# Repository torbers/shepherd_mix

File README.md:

# shepherd_mix
modular music hardware system for everyone

---

License:

<a href="https://github.com/torbers/shepherd_mix">Shepherd Mix design specifications</a> © 2025 by <a href="http://sambkothe.com">Sam Kothe (torbers)</a> are licensed under <a href="https://creativecommons.org/licenses/by-sa/4.0/">CC BY-SA 4.0</a>

<a href="https://github.com/torbers/shepherd_mix">Shepherd Mix code</a> © 2025 by <a href="http://sambkothe.com">Sam Kothe (torbers)</a> is licensed under <a href="https://creativecommons.org/licenses/by-sa/4.0/">CC BY-SA 4.0</a>

<a href="https://github.com/torbers/shepherd_mix">Shepherd Mix PCB designs</a> © 2025 by <a href="http://sambkothe.com">Sam Kothe (torbers)</a> are licensed under <a href="https://creativecommons.org/licenses/by-nc-sa/4.0/">CC BY-NC-SA 4.0</a>

<a href="https://github.com/torbers/shepherd_mix">Shepherd Mix art</a> © 2025 by <a href="http://sambkothe.com">Sam Kothe (torbers)</a> is licensed under <a href="https://creativecommons.org/licenses/by-nc-sa/4.0/">CC BY-NC-SA 4.0</a>

This means that you may design, manufacture, and sell products compatible with Shepherd Mix or using its code in accordance with [open source standards](https://opensource.org/osd), but you may not sell my PCB source files, artistic designs, or products made with them. In any case, you must give [appropriate credit](https://creativecommons.org/licenses/by-sa/4.0/#ref-appropriate-credit).

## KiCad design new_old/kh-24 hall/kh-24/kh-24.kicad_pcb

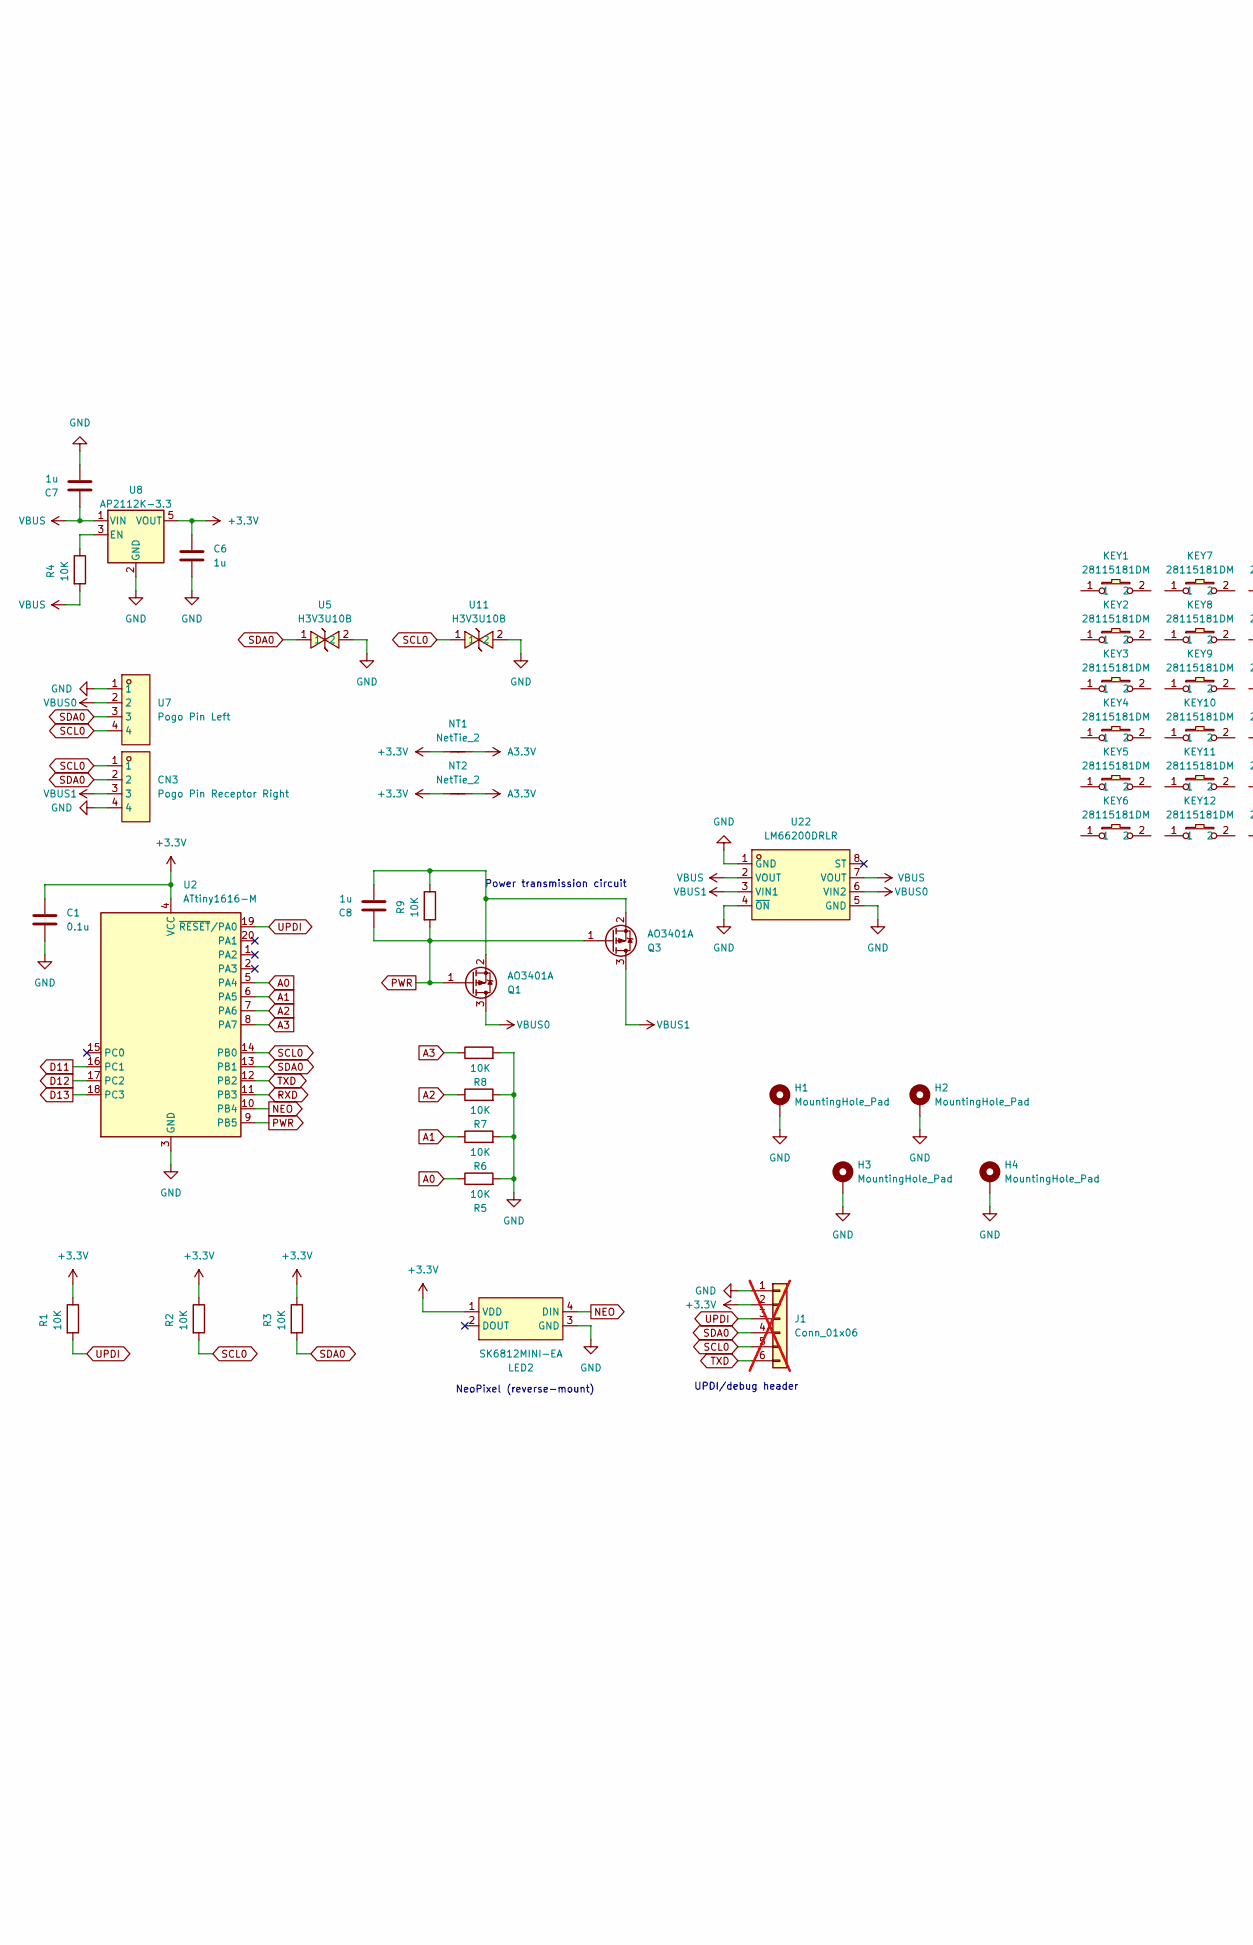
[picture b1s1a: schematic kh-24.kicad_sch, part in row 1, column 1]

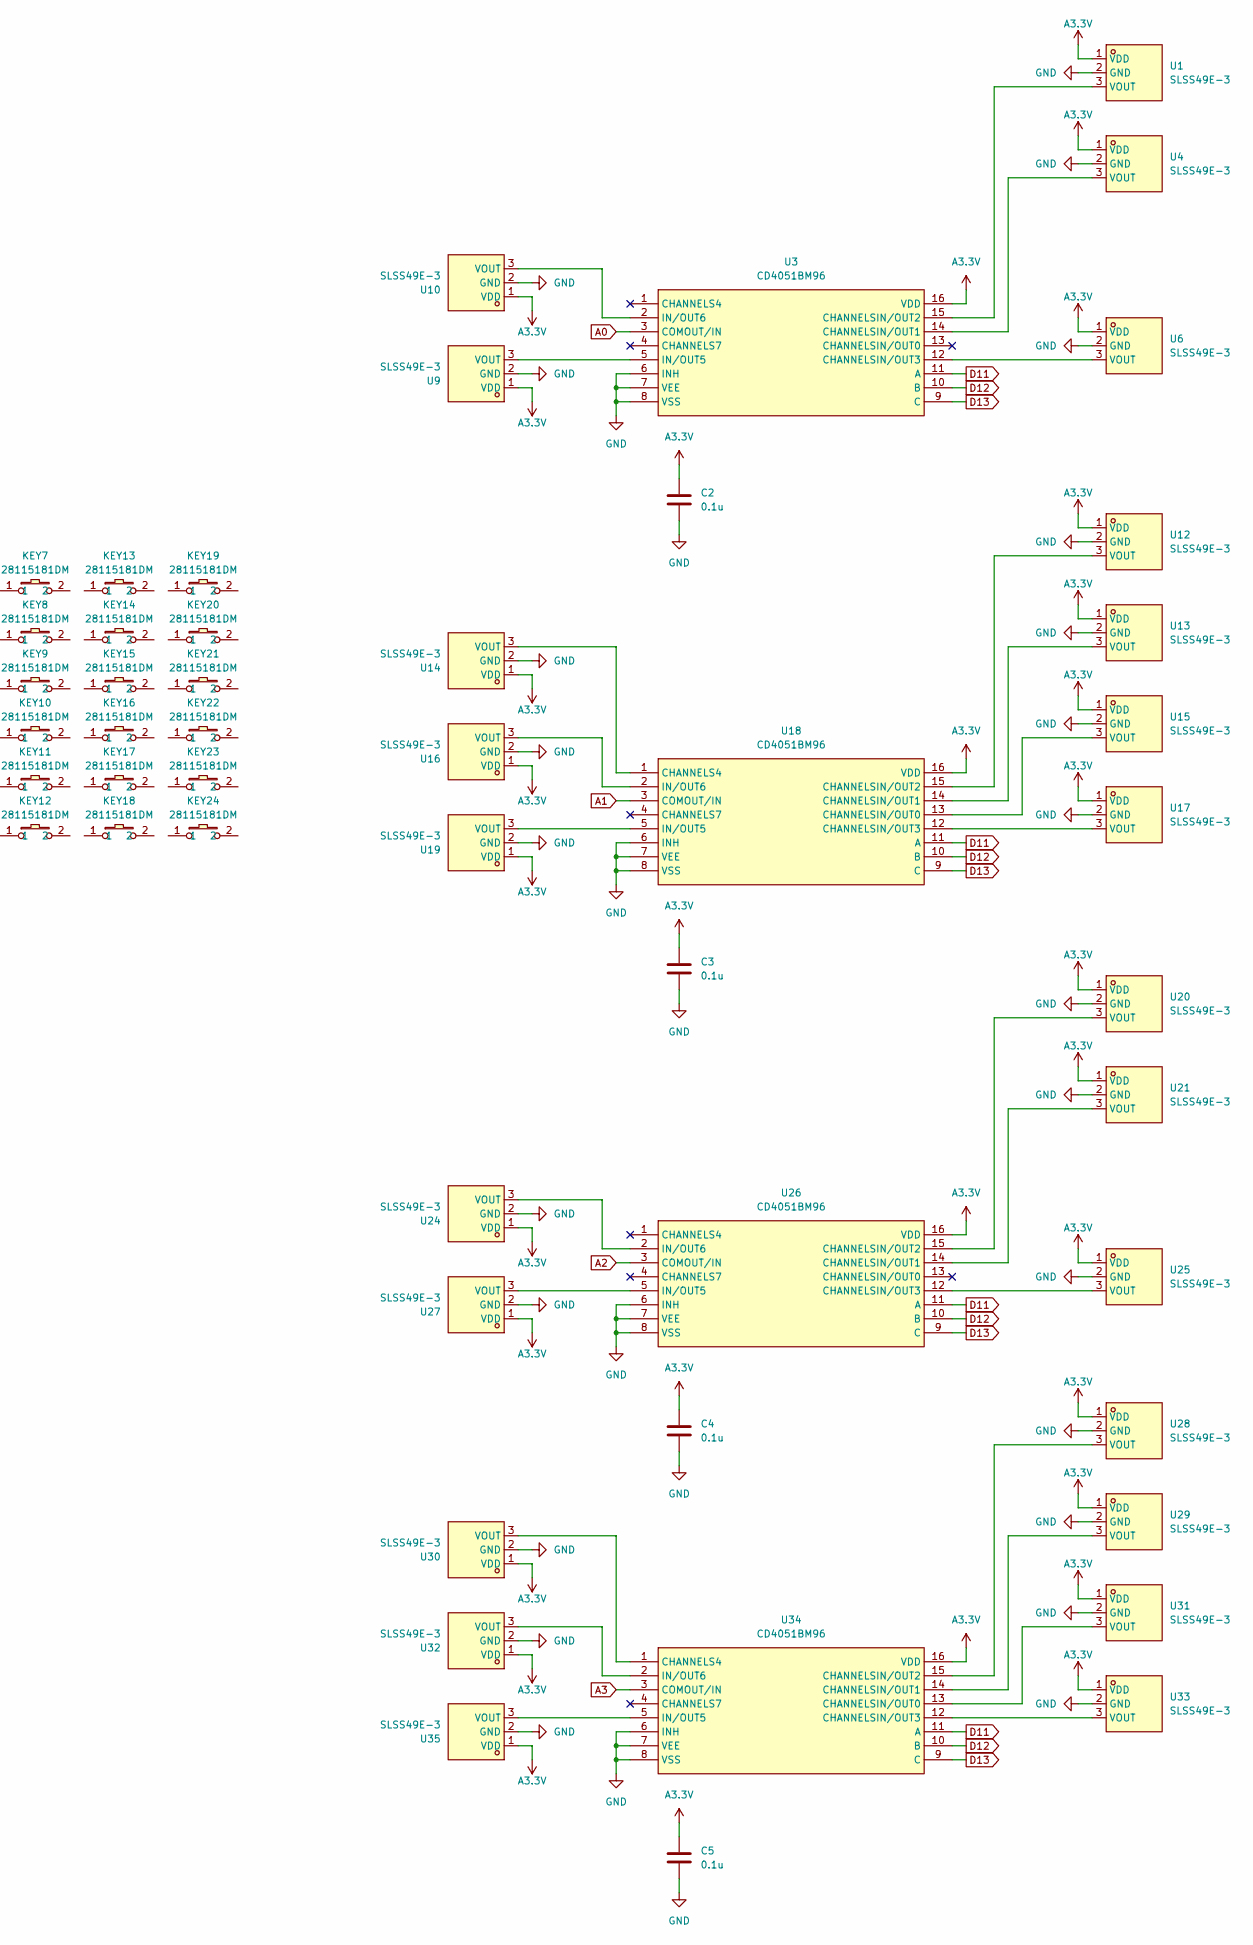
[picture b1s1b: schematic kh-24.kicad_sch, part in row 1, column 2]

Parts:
C1, C2, C3, C4, C5: 0.1u; C_0402_1005Metric
C6, C7, C8: 1u; C_0402_1005Metric
CN3: Pogo Pin Receptor Right; CONN-SMD_YZ199315035T-04025-01; LCSC Part C5296825
H1, H2, H3, H4: MountingHole_Pad; MountingHole_2.7mm_M2.5_DIN965_Pad_TopBottom
J1: Conn_01x06; PinHeader_1x06_P2.54mm_Vertical; not fitted
KEY1, KEY2, KEY3, KEY4, KEY5, KEY6, KEY7, KEY8, KEY9, KEY10, KEY11, KEY12, KEY13, KEY14, KEY15, KEY16, KEY17, KEY18, KEY19, KEY20, KEY21, KEY22, KEY23, KEY24: 28115181DM; hall_key_footprint; LCSC Part C47121944
LED2: SK6812MINI-EA; LED-SMD_4P-L3.2-W2.8_SK6812MINI-EA; LCSC Part C5378731
NT1, NT2: NetTie_2; NetTie-2_SMD_Pad0.5mm
Q1, Q3: AO3401A; SOT-23
R1, R2, R3, R4, R9: 10K; R_0402_1005Metric
R5, R6, R7, R8: 10K; R_0402_1005Metric_Pad0.72x0.64mm_HandSolder
U1, U4, U6, U9, U10, U12, U13, U14, U15, U16, U17, U19, U20, U21, U24, U25, U27, U28, U29, U30, U31, U32, U33, U35: SLSS49E-3; SLSS49E_Hall_Switch_MX; LCSC Part C2904393
U2: ATtiny1616-M; VQFN-20-1EP_3x3mm_P0.4mm_EP1.7x1.7mm
U3, U18, U26, U34: CD4051BM96; SOIC-16_L9.9-W3.9-P1.27-LS6.0-BL; LCSC Part C21379
U5, U11: H3V3U10B; DFN1006-2L-BI; LCSC Part C20615782
U7: Pogo Pin Left; CONN-SMD_4P-L11.0-W5.5-P2.50_YZ165615055F-04025-01; LCSC Part C5296819
U8: AP2112K-3.3; SOT-23-5
U22: LM66200DRLR; SOT-583-8_L2.1-W1.2-P0.50-LS1.6-BL; LCSC Part C3235556

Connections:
+3.3V: C1.1, C6.1, J1.2, LED2.1 (VDD), NT1.1, NT2.1, R1.1, R2.1, R3.1, U2.4 (VCC), U8.5 (VOUT)
A0: R5.1, U2.5 (PA4), U3.3 (COMOUT/IN)
A1: R6.1, U2.6 (PA5), U18.3 (COMOUT/IN)
A2: R7.1, U2.7 (PA6), U26.3 (COMOUT/IN)
A3: R8.1, U2.8 (PA7), U34.3 (COMOUT/IN)
A3.3V: C2.1, C3.1, C4.1, C5.1, NT1.2, NT2.2, U1.1 (VDD), U3.16 (VDD), U4.1 (VDD), U6.1 (VDD), U9.1 (VDD), U10.1 (VDD), U12.1 (VDD), U13.1 (VDD), U14.1 (VDD), U15.1 (VDD), U16.1 (VDD), U17.1 (VDD), U18.16 (VDD), U19.1 (VDD), U20.1 (VDD), U21.1 (VDD), U24.1 (VDD), U25.1 (VDD), U26.16 (VDD), U27.1 (VDD), U28.1 (VDD), U29.1 (VDD), U30.1 (VDD), U31.1 (VDD), U32.1 (VDD), U33.1 (VDD), U34.16 (VDD), U35.1 (VDD)
D11: U2.16 (PC1), U3.11 (A), U18.11 (A), U26.11 (A), U34.11 (A)
D12: U2.17 (PC2), U3.10 (B), U18.10 (B), U26.10 (B), U34.10 (B)
D13: U2.18 (PC3), U3.9 (C), U18.9 (C), U26.9 (C), U34.9 (C)
GND: C1.2, C2.2, C3.2, C4.2, C5.2, C6.2, C7.2, CN3.4, H1.1, H2.1, H3.1, H4.1, J1.1, LED2.3 (GND), R5.2, R6.2, R7.2, R8.2, U1.2 (GND), U2.3 (GND), U2.21 (GND), U3.6 (INH), U3.7 (VEE), U3.8 (VSS), U4.2 (GND), U5.2, U6.2 (GND), U7.1, U8.2 (GND), U9.2 (GND), U10.2 (GND), U11.2, U12.2 (GND), U13.2 (GND), U14.2 (GND), U15.2 (GND), U16.2 (GND), U17.2 (GND), U18.6 (INH), U18.7 (VEE), U18.8 (VSS), U19.2 (GND), U20.2 (GND), U21.2 (GND), U22.1 (GND), U22.4 (~ON), U22.5 (GND), U24.2 (GND), U25.2 (GND), U26.6 (INH), U26.7 (VEE), U26.8 (VSS), U27.2 (GND), U28.2 (GND), U29.2 (GND), U30.2 (GND), U31.2 (GND), U32.2 (GND), U33.2 (GND), U34.6 (INH), U34.7 (VEE), U34.8 (VSS), U35.2 (GND)
NEO: LED2.4 (DIN), U2.10 (PB4)
unnamed: C8.2, Q1.2 (S), Q3.2 (S), R9.1
unnamed: U1.3 (VOUT), U3.15 (CHANNELSIN/OUT2)
unnamed: U3.14 (CHANNELSIN/OUT1), U4.3 (VOUT)
unnamed: U3.12 (CHANNELSIN/OUT3), U6.3 (VOUT)
unnamed: U3.5 (IN/OUT5), U9.3 (VOUT)
unnamed: R4.1, U8.3 (EN)
unnamed: U3.2 (IN/OUT6), U10.3 (VOUT)
unnamed: U12.3 (VOUT), U18.15 (CHANNELSIN/OUT2)
unnamed: U13.3 (VOUT), U18.14 (CHANNELSIN/OUT1)
unnamed: U14.3 (VOUT), U18.1 (CHANNELS4)
unnamed: U15.3 (VOUT), U18.13 (CHANNELSIN/OUT0)
unnamed: U16.3 (VOUT), U18.2 (IN/OUT6)
unnamed: U17.3 (VOUT), U18.12 (CHANNELSIN/OUT3)
unnamed: U18.5 (IN/OUT5), U19.3 (VOUT)
unnamed: U20.3 (VOUT), U26.15 (CHANNELSIN/OUT2)
unnamed: U21.3 (VOUT), U26.14 (CHANNELSIN/OUT1)
unnamed: U24.3 (VOUT), U26.2 (IN/OUT6)
unnamed: U25.3 (VOUT), U26.12 (CHANNELSIN/OUT3)
unnamed: U26.5 (IN/OUT5), U27.3 (VOUT)
unnamed: U28.3 (VOUT), U34.15 (CHANNELSIN/OUT2)
unnamed: U29.3 (VOUT), U34.14 (CHANNELSIN/OUT1)
unnamed: U30.3 (VOUT), U34.1 (CHANNELS4)
unnamed: U31.3 (VOUT), U34.13 (CHANNELSIN/OUT0)
unnamed: U32.3 (VOUT), U34.2 (IN/OUT6)
unnamed: U33.3 (VOUT), U34.12 (CHANNELSIN/OUT3)
unnamed: U34.5 (IN/OUT5), U35.3 (VOUT)
PWR: C8.1, Q1.1 (G), Q3.1 (G), R9.2, U2.9 (PB5)
RXD: U2.11 (PB3)
SCL0: CN3.1, J1.5, R2.2, U2.14 (PB0), U7.4, U11.1
SDA0: CN3.2, J1.4, R3.2, U2.13 (PB1), U5.1, U7.3
TXD: J1.6, U2.12 (PB2)
UPDI: J1.3, R1.2, U2.19 (~RESET/PA0)
VBUS: C7.1, R4.2, U8.1 (VIN), U22.2 (VOUT), U22.7 (VOUT)
VBUS0: Q1.3 (D), U7.2, U22.6 (VIN2)
VBUS1: CN3.3, Q3.3 (D), U22.3 (VIN1)

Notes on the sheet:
Power transmission circuit
NeoPixel (reverse-mount)
UPDI/debug header

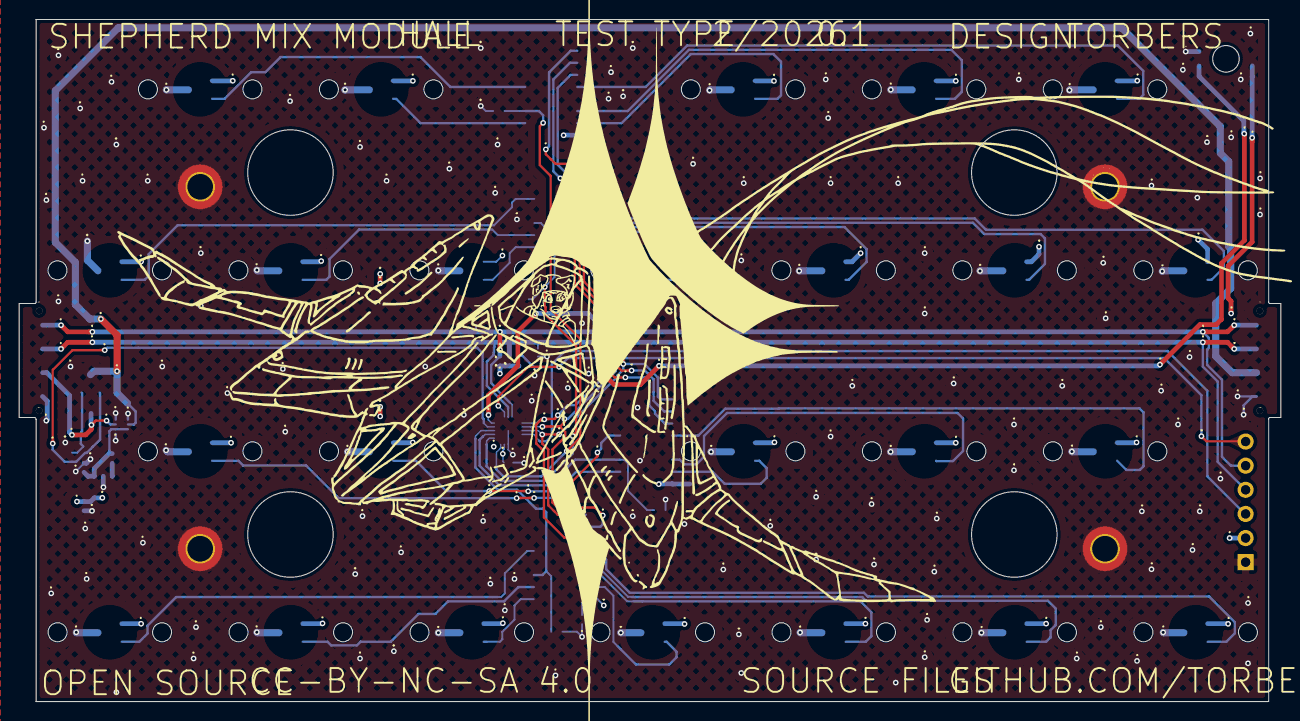
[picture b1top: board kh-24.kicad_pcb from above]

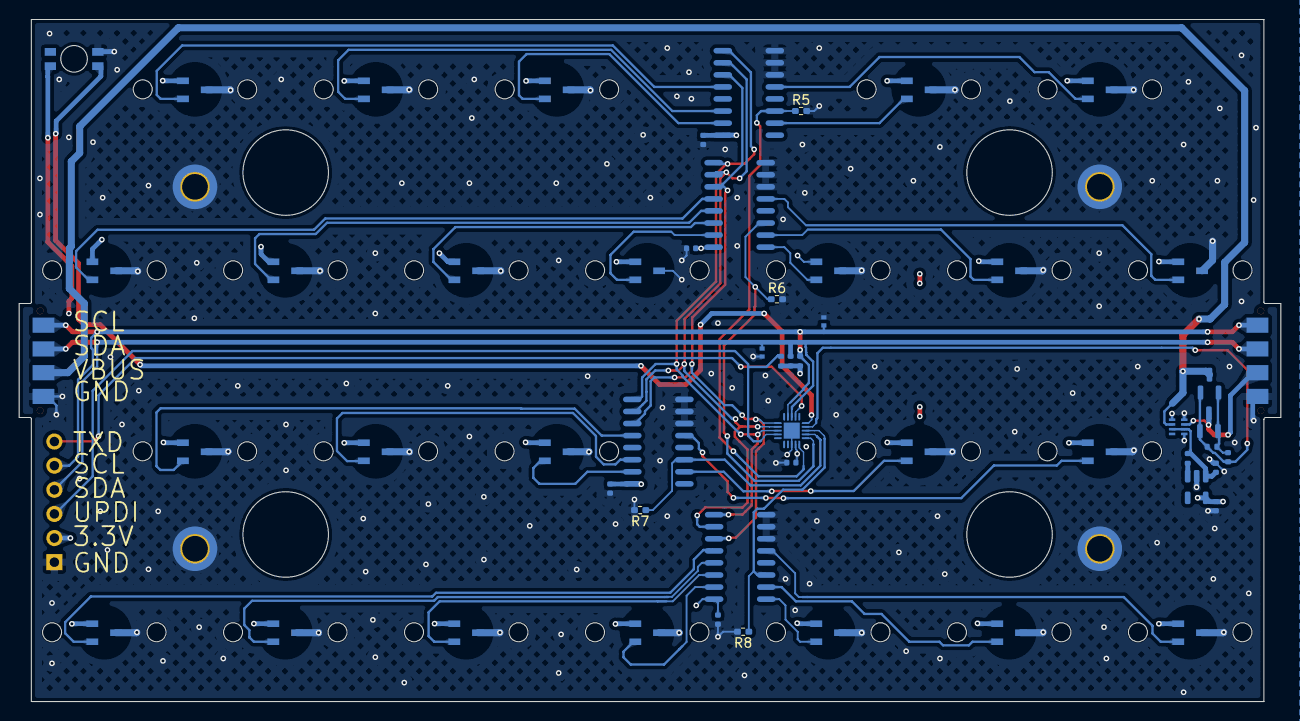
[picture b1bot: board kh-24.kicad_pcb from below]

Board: 4 copper layers, 132.8 x 71.8 mm, 86 parts (60 on the bottom side), 45 nets.

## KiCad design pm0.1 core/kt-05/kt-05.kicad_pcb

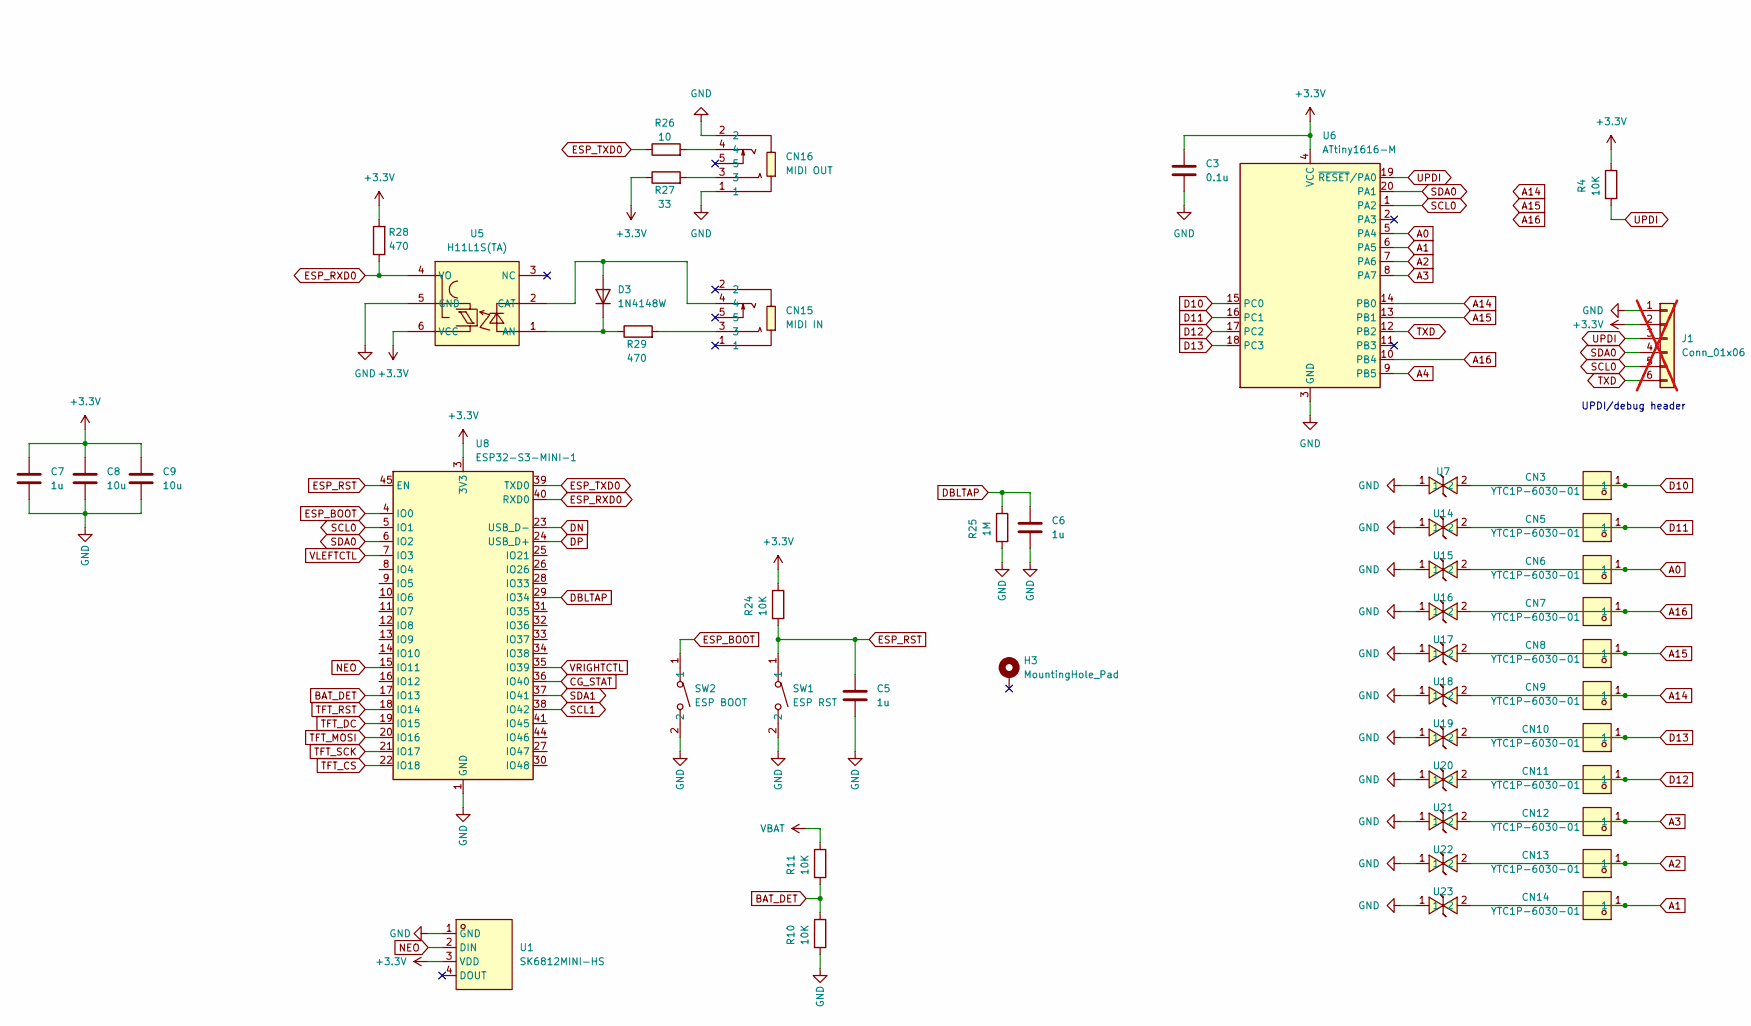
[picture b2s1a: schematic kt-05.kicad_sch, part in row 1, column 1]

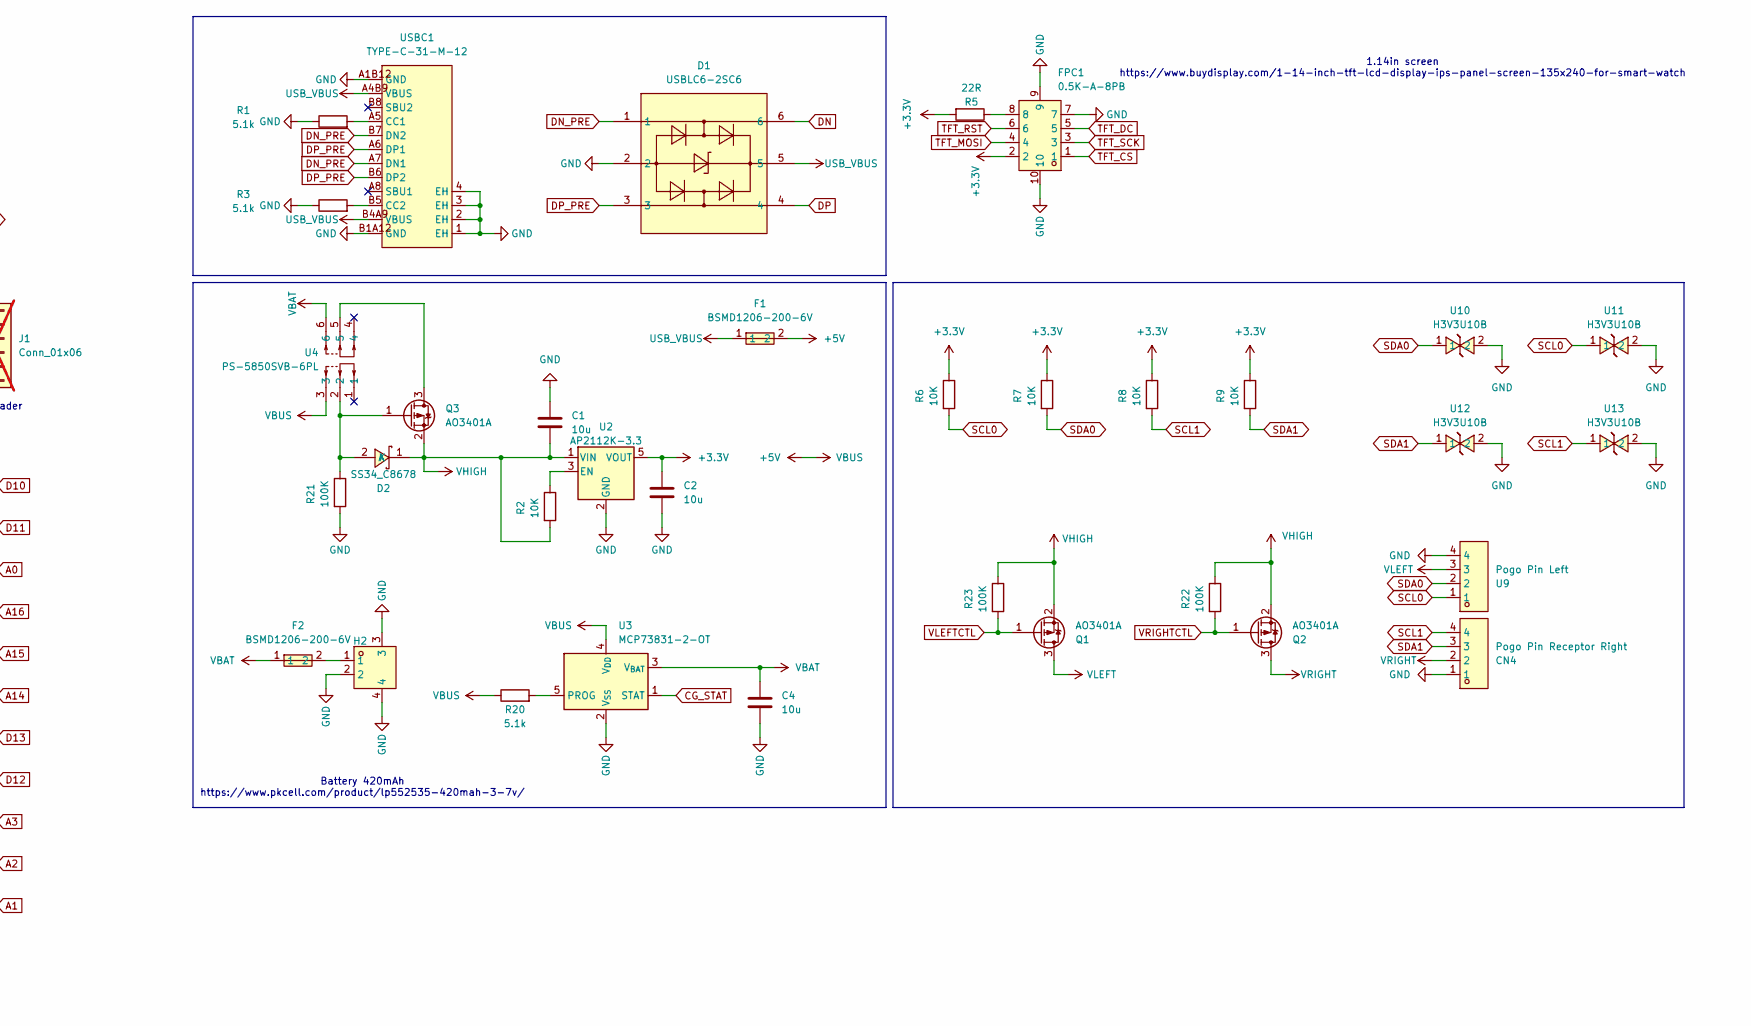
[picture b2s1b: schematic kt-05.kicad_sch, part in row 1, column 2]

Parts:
C1, C2, C4, C8, C9: 10u; C_0402_1005Metric
C3: 0.1u; C_0402_1005Metric
C5, C6, C7: 1u; C_0402_1005Metric
CN3, CN5, CN6, CN7, CN8, CN9, CN10, CN11, CN12, CN13, CN14: YTC1P-6030-01; SMD-1_BD2.0-H10.0; LCSC Part C5221285
CN4: Pogo Pin Receptor Right; CONN-SMD_YZ199315035T-04025-01; LCSC Part C5296825
CN15: MIDI IN; AUDIO-SMD_PJ-327A5JJ; LCSC Part C668605
CN16: MIDI OUT; AUDIO-SMD_PJ-327A5JJ; LCSC Part C668605
D1: USBLC6-2SC6; SOT-23-6_L2.9-W1.6-P0.95-LS2.8-BL; LCSC Part C7519
D2: SS34_C8678; SMA_L4.3-W2.6-LS5.2-RD; LCSC Part C8678
D3: 1N4148W; D_SOD-123
F1, F2: BSMD1206-200-6V; F1206; LCSC Part C883134
FPC1: 0.5K-A-8PB; FPC-SMD_8P-P0.50_HDGC_0.5K-A-8PB; LCSC Part C2914134
H2: WAFER-PH2.0-2PWB; CONN-SMD_2P-P2.00_XUNPU_WAFER-PH2.0-2PWB; LCSC Part C3029440
H3: MountingHole_Pad; MountingHole_2.7mm_M2.5_DIN965_Pad_TopBottom
J1: Conn_01x06; PinHeader_1x06_P2.54mm_Vertical; not fitted
Q1, Q2, Q3: AO3401A; SOT-23
R1, R3, R20: 5.1k; R_0402_1005Metric
R2, R4, R6, R7, R8, R9, R10, R11, R24: 10K; R_0402_1005Metric
R5: 22R; R_0402_1005Metric
R21, R22, R23: 100K; R_0402_1005Metric
R25: 1M; R_0402_1005Metric
R26: 10; R_0402_1005Metric
R27: 33; R_0402_1005Metric
R28, R29: 470; R_0402_1005Metric
SW1: ESP RST; SW-SMD_L3.9-W3.0-P4.45; LCSC Part C720477
SW2: ESP BOOT; SW-SMD_L3.9-W3.0-P4.45; LCSC Part C720477
U1: SK6812MINI-HS; LED-SMD_4P-L3.5-W3.5-BR_SK6812MINI-HS; LCSC Part C2922787
U2: AP2112K-3.3; SOT-23-5
U3: MCP73831-2-OT; SOT-23-5; LCSC ID C424093
U4: PS-5850SVB-6PL; SW-SMD_6P-L5.8-W5.8-P2.00-LS11.3; LCSC Part C5155567
U5: H11L1S(TA); SMD-6_L7.3-W6.5-P2.54-LS10.2-BL; LCSC Part C78589
U6: ATtiny1616-M; VQFN-20-1EP_3x3mm_P0.4mm_EP1.7x1.7mm
U7, U10, U11, U12, U13, U14, U15, U16, U17, U18, U19, U20, U21, U22, U23: H3V3U10B; DFN1006-2L-BI; LCSC Part C20615782
U8: ESP32-S3-MINI-1; ESP32-S2-MINI-1
U9: Pogo Pin Left; CONN-SMD_4P-L11.0-W5.5-P2.50_YZ165615055F-04025-01; LCSC Part C5296819
USBC1: TYPE-C-31-M-12; USB-C_SMD-TYPE-C-31-M-12_1; LCSC Part C165948

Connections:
+3.3V: C2.1, C3.1, C7.1, C8.1, C9.1, FPC1.2, J1.2, R4.1, R5.2, R6.1, R7.1, R8.1, R9.1, R24.1, R27.1, R28.2, U1.3 (VDD), U2.5 (VOUT), U5.6 (VCC), U6.4 (VCC), U8.3 (3V3)
A0: CN6.1, U6.5 (PA4), U15.2
A1: CN14.1, U6.6 (PA5), U23.2
A2: CN13.1, U6.7 (PA6), U22.2
A3: CN12.1, U6.8 (PA7), U21.2
A4: U6.9 (PB5)
A14: CN9.1, U6.14 (PB0), U18.2
A15: CN8.1, U6.13 (PB1), U17.2
A16: CN7.1, U6.10 (PB4), U16.2
BAT_DET: R10.1, R11.2, U8.17 (IO13)
CG_STAT: U3.1 (STAT), U8.36 (IO40)
D10: CN3.1, U6.15 (PC0), U7.2
D11: CN5.1, U6.16 (PC1), U14.2
D12: CN11.1, U6.17 (PC2), U20.2
D13: CN10.1, U6.18 (PC3), U19.2
DBLTAP: C6.1, R25.1, U8.29 (IO34)
DN: D1.6, U8.23 (USB_D-)
DN_PRE: D1.1, USBC1.A7 (DN1), USBC1.B7 (DN2)
DP: D1.4, U8.24 (USB_D+)
DP_PRE: D1.3, USBC1.A6 (DP1), USBC1.B6 (DP2)
ESP_BOOT: SW2.1, U8.4 (IO0)
ESP_RST: C5.1, R24.2, SW1.1, U8.45 (EN)
ESP_RXD0: R28.1, U5.4 (VO), U8.40 (RXD0)
ESP_TXD0: R26.1, U8.39 (TXD0)
GND: C1.2, C2.2, C3.2, C4.2, C5.2, C6.2, C7.2, C8.2, C9.2, CN4.1, CN16.1, CN16.2, D1.2, FPC1.7, FPC1.9, FPC1.10, H2.2, H2.3, H2.4, J1.1, R1.1, R3.1, R10.2, R21.2, R25.2, SW1.2, SW2.2, U1.1 (GND), U2.2 (GND), U3.2 (V_{SS}), U5.5 (GND), U6.3 (GND), U6.21 (GND), U7.1, U8.1 (GND), U8.2 (GND), U8.42 (GND), U8.43 (GND), U8.46 (GND), U8.47 (GND), U8.48 (GND), U8.49 (GND), U8.50 (GND), U8.51 (GND), U8.52 (GND), U8.53 (GND), U8.54 (GND), U8.55 (GND), U8.56 (GND), U8.57 (GND), U8.58 (GND), U8.59 (GND), U8.60 (GND), U8.61 (GND), U8.62 (GND), U8.63 (GND), U8.64 (GND), U8.65 (GND), U9.4, U10.2, U11.2, U12.2, U13.2, U14.1, U15.1, U16.1, U17.1, U18.1, U19.1, U20.1, U21.1, U22.1, U23.1, USBC1.1 (EH), USBC1.2 (EH), USBC1.3 (EH), USBC1.4 (EH), USBC1.A1B12 (GND), USBC1.B1A12 (GND)
NEO: U1.2 (DIN), U8.15 (IO11)
unnamed: CN15.3, R29.2
unnamed: CN16.3, R27.2
unnamed: CN16.4, R26.2
unnamed: D2.2 (A), Q3.1 (G), R21.1, U4.2
unnamed: CN15.4, D3.2 (A), U5.2 (CAT)
unnamed: D3.1 (K), R29.1, U5.1 (AN)
unnamed: F2.2, H2.1
unnamed: FPC1.8, R5.1
unnamed: Q3.3 (D), U4.5
unnamed: R2.1, U2.3 (EN)
unnamed: R20.2, U3.5 (PROG)
unnamed: R1.2, USBC1.A5 (CC1)
unnamed: R3.2, USBC1.B5 (CC2)
SCL0: J1.5, R6.2, U6.1 (PA2), U8.5 (IO1), U9.1, U11.1
SCL1: CN4.4, R8.2, U8.38 (IO42), U13.1
SDA0: J1.4, R7.2, U6.20 (PA1), U8.6 (IO2), U9.2, U10.1
SDA1: CN4.3, R9.2, U8.37 (IO41), U12.1
TFT_CS: FPC1.1, U8.22 (IO18)
TFT_DC: FPC1.5, U8.19 (IO15)
TFT_MOSI: FPC1.4, U8.20 (IO16)
TFT_RST: FPC1.6, U8.18 (IO14)
TFT_SCK: FPC1.3, U8.21 (IO17)
TXD: J1.6, U6.12 (PB2)
UPDI: J1.3, R4.2, U6.19 (~RESET/PA0)
USB_VBUS: D1.5, F1.1, USBC1.A4B9 (VBUS), USBC1.B4A9 (VBUS)
VBAT: C4.1, F2.1, R11.1, U3.3 (V_{BAT}), U4.6
VLEFT: Q1.3 (D), U9.3
VLEFTCTL: Q1.1 (G), R23.2, U8.7 (IO3)
VRIGHT: CN4.2, Q2.3 (D)
VRIGHTCTL: Q2.1 (G), R22.2, U8.35 (IO39)

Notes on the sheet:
UPDI/debug header
1.14in screen https://www.buydisplay.com/1-14-inch-tft-lcd-display-ips-panel-screen-135x240-for-smart-watch
Battery 420mAh https://www.pkcell.com/product/lp552535-420mah-3-7v/

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
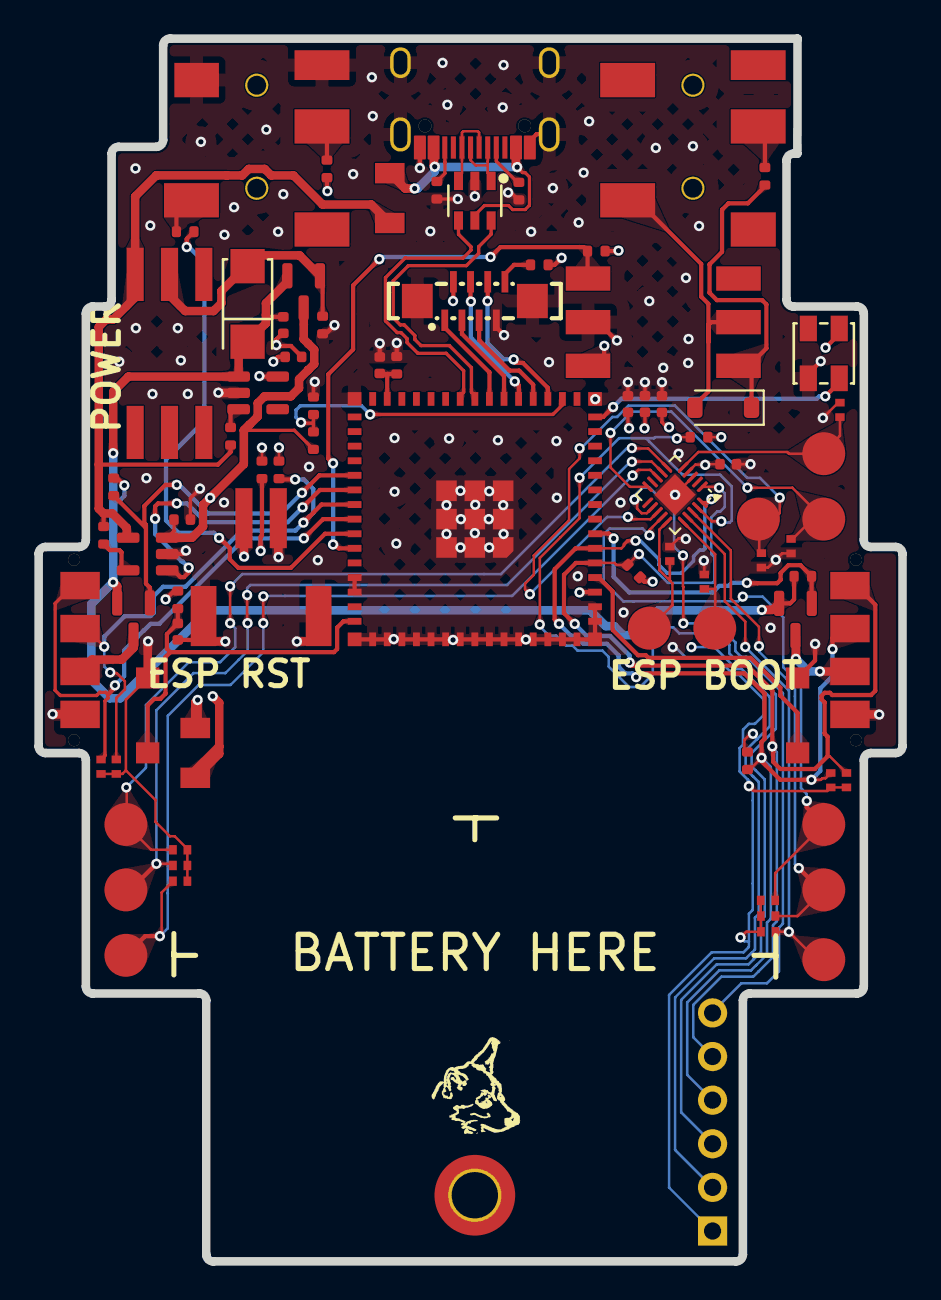
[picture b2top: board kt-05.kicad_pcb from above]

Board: 4 copper layers, 50.3 x 71.2 mm, 82 parts (0 on the bottom side), 57 nets.

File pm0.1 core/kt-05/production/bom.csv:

Designator,Footprint,Quantity,Value,LCSC Part #
"C1, C2, C4, C8, C9",0402,5,10u,
C3,0402,1,0.1u,
"C5, C6, C7",0402,3,1u,
"CN10, CN11, CN12, CN13, CN14, CN3, CN5, CN6, CN7, CN8, CN9",SMD-1_BD2.0-H10.0,11,YTC1P-6030-01,C5221285
CN15,AUDIO-SMD_PJ-327A5JJ,1,MIDI IN,C668605
CN16,AUDIO-SMD_PJ-327A5JJ,1,MIDI OUT,C668605
CN4,CONN-SMD_YZ199315035T-04025-01,1,Pogo Pin Receptor Right,C5296825
D1,SOT-23-6_L2.9-W1.6-P0.95-LS2.8-BL,1,USBLC6-2SC6,C7519
D2,SMA_L4.3-W2.6-LS5.2-RD,1,SS34_C8678,C8678
D3,D_SOD-123,1,1N4148W,
"F1, F2",F1206,2,BSMD1206-200-6V,C883134
FPC1,FPC-SMD_8P-P0.50_HDGC_0.5K-A-8PB,1,0.5K-A-8PB,C2914134
H2,CONN-SMD_2P-P2.00_XUNPU_WAFER-PH2.0-2PWB,1,WAFER-PH2.0-2PWB,C3029440
"Q1, Q2, Q3",SOT-23,3,AO3401A,
"R1, R20, R3",0402,3,5.1k,
"R10, R11, R2, R24, R4, R6, R7, R8, R9",0402,9,10K,
"R21, R22, R23",0402,3,100K,
R25,0402,1,1M,
R26,0402,1,10,
R27,0402,1,33,
"R28, R29",0402,2,470,
R5,0402,1,22R,
SW1,SW-SMD_L3.9-W3.0-P4.45,1,ESP RST,C720477
SW2,SW-SMD_L3.9-W3.0-P4.45,1,ESP BOOT,C720477
U1,LED-SMD_4P-L3.5-W3.5-BR_SK6812MINI-HS,1,SK6812MINI-HS,C2922787
"U10, U11, U12, U13, U14, U15, U16, U17, U18, U19, U20, U21, U22, U23, U7",DFN1006-2L-BI,15,H3V3U10B,C20615782
U2,SOT-23-5,1,AP2112K-3.3,
U3,SOT-23-5,1,MCP73831-2-OT,
U4,SW-SMD_6P-L5.8-W5.8-P2.00-LS11.3,1,PS-5850SVB-6PL,C5155567
U5,SMD-6_L7.3-W6.5-P2.54-LS10.2-BL,1,H11L1S(TA),C78589
U6,VQFN-20-1EP_3x3mm_P0.4mm_EP1.7x1.7mm,1,ATtiny1616-M,
U8,ESP32-S2-MINI-1,1,ESP32-S3-MINI-1,
U9,CONN-SMD_4P-L11.0-W5.5-P2.50_YZ165615055F-04025-01,1,Pogo Pin Left,C5296819
USBC1,USB-C_SMD-TYPE-C-31-M-12_1,1,TYPE-C-31-M-12,C165948

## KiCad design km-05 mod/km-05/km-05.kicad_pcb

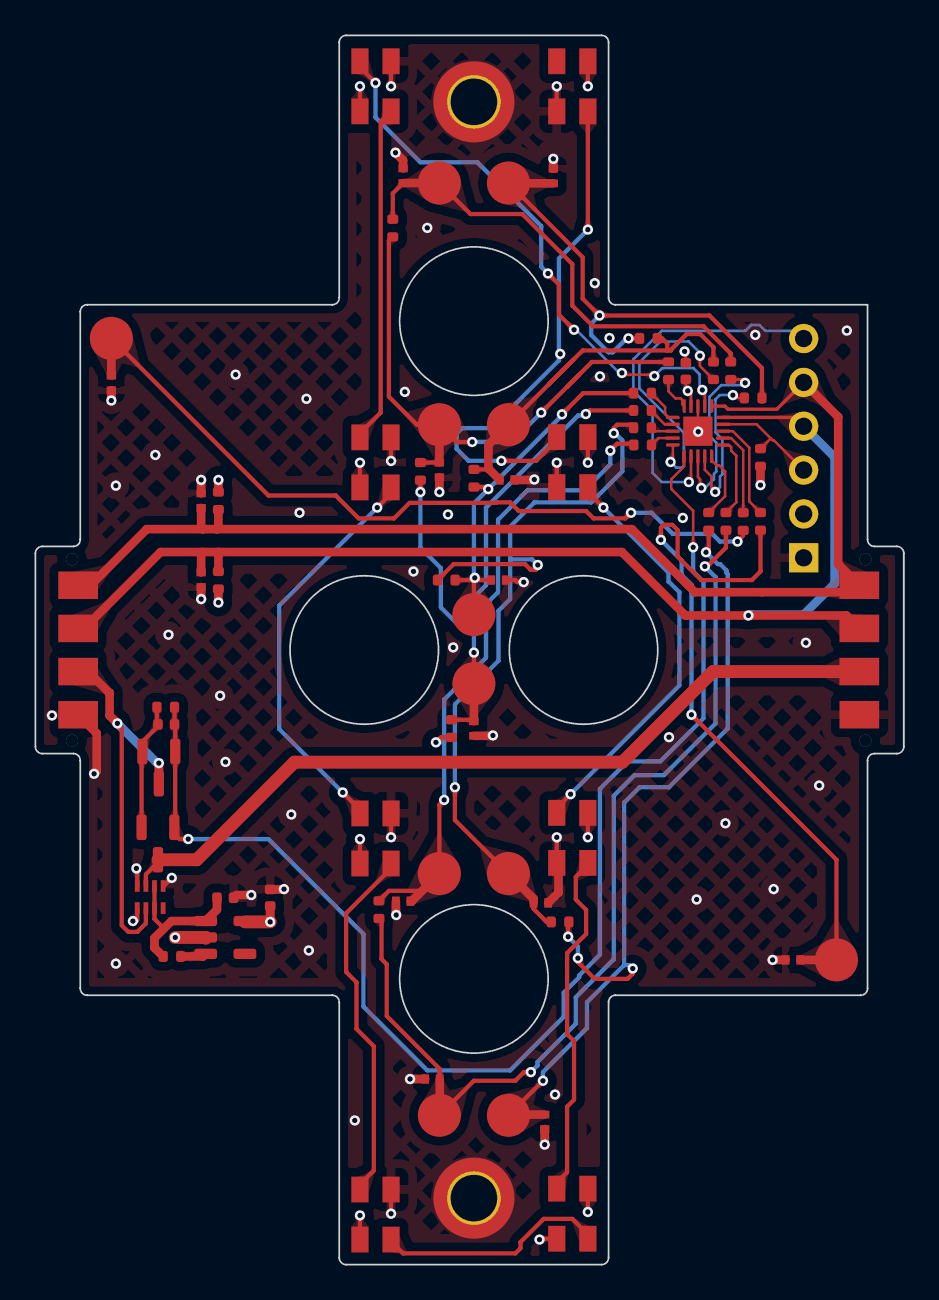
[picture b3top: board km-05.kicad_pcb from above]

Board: 4 copper layers, 50.3 x 71.2 mm, 73 parts (0 on the bottom side), 44 nets.

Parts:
C1: 0.1u; C_0402_1005Metric
C6, C7: 10u; C_0402_1005Metric
C8: 1u; C_0402_1005Metric
CN1, CN2, CN4, CN5, CN6, CN7, CN8, CN9, CN10, CN11, CN12, CN14: YTC1P-6030-01; SMD-1_BD2.0-H10.0
CN3: Pogo Pin Receptor Right; CONN-SMD_YZ199315035T-04025-01
H1, H2: MountingHole_Pad; MountingHole_2.7mm_M2.5_DIN965_Pad_TopBottom
J1: Conn_01x06; PinHeader_1x06_P2.54mm_Vertical
Q3, Q4: AO3401A; SOT-23
R1, R2, R3, R4, R21, R22, R23, R24, R25, R26, R27, R28, R29: 10K; R_0402_1005Metric
R9, R10, R11, R12, R13, R14, R15, R16, R17, R18, R19, R20: 0R; R_0402_1005Metric
U1, U19, U20, U21, U22, U23, U24, U25: SK6812MINI-HS; LED-SMD_4P-L3.5-W3.5-BR_SK6812MINI-HS
U2: ATtiny1616-M; VQFN-20-1EP_3x3mm_P0.4mm_EP1.7x1.7mm
U3, U4, U5, U6, U9, U10, U11, U12, U13, U14, U15, U16, U17, U18: H3V3U10B; DFN1006-2L-BI
U7: Pogo Pin Left; CONN-SMD_4P-L11.0-W5.5-P2.50_YZ165615055F-04025-01
U8: AP2112K-3.3; SOT-23-5
U26: LM66200DRLR; SOT-583-8_L2.1-W1.2-P0.50-LS1.6-BL

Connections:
+3.3V: C1.1, C6.1, J1.2, R1.1, R2.1, R3.1, U1.3 (VDD), U2.4 (VCC), U8.5 (VOUT), U19.3 (VDD), U20.3 (VDD), U21.3 (VDD), U22.3 (VDD), U23.3 (VDD), U24.3 (VDD), U25.3 (VDD)
A0: R9.1, U2.5 (PA4)
A1: R10.1, U2.6 (PA5)
A2: R11.1, U2.7 (PA6)
A3: R12.1, U2.8 (PA7)
A4: R20.1, U2.9 (PB5)
A14: R17.1, U2.14 (PB0)
A15: R18.1, U2.13 (PB1)
A16: R19.1, U2.10 (PB4)
D10: R16.1, U2.15 (PC0)
D11: R15.1, U2.16 (PC1)
D12: R14.1, U2.17 (PC2)
D13: R13.1, U2.18 (PC3)
GND: C1.2, C6.2, C7.2, CN3.1, H1.1, H2.1, J1.1, U1.1 (GND), U2.3 (GND), U2.21 (GND), U3.1, U4.1, U5.2, U6.1, U7.4, U8.2 (GND), U9.1, U10.1, U11.2, U12.1, U13.1, U14.1, U15.1, U16.1, U17.1, U18.1, U19.1 (GND), U20.1 (GND), U21.1 (GND), U22.1 (GND), U23.1 (GND), U24.1 (GND), U25.1 (GND), U26.1 (GND), U26.4 (~ON), U26.5 (GND)
NEO: U1.2 (DIN), U2.2 (PA3)
unnamed: CN1.1, R9.2, R21.2, R22.1, U15.2
unnamed: CN2.1, R11.2, R22.2, R23.1, U14.2
unnamed: CN4.1, R20.2, R23.2, R24.1, U13.2
unnamed: CN5.1, R15.2, R24.2, U12.2
unnamed: CN6.1, R16.2, R28.2, U9.2
unnamed: CN7.1, R12.2, R27.2, R28.1, U6.2
unnamed: CN8.1, R10.2, R26.2, R27.1, U4.2
unnamed: CN9.1, R19.2, R25.2, R26.1, U3.2
unnamed: CN10.1, R14.2, U18.2
unnamed: CN11.1, R13.2, U17.2
unnamed: CN12.1, R18.2, R21.1, U16.2
unnamed: CN14.1, R17.2, R25.1, U10.2
unnamed: C8.2, Q3.2 (S), Q4.2 (S), R29.1
unnamed: U1.4 (DOUT), U19.2 (DIN)
unnamed: R4.1, U8.3 (EN)
unnamed: U19.4 (DOUT), U20.2 (DIN)
unnamed: U20.4 (DOUT), U21.2 (DIN)
unnamed: U21.4 (DOUT), U22.2 (DIN)
unnamed: U22.4 (DOUT), U23.2 (DIN)
unnamed: U23.4 (DOUT), U24.2 (DIN)
unnamed: U24.4 (DOUT), U25.2 (DIN)
PWR: C8.1, Q3.1 (G), Q4.1 (G), R29.2, U2.11 (PB3)
SCL0: CN3.4, J1.5, R2.2, U2.1 (PA2), U7.1, U11.1
SDA0: CN3.3, J1.4, R3.2, U2.20 (PA1), U5.1, U7.2
TXD: J1.6, U2.12 (PB2)
UPDI: J1.3, R1.2, U2.19 (~RESET/PA0)
VBUS: C7.1, R4.2, U8.1 (VIN), U26.2 (VOUT), U26.7 (VOUT)
VBUS0: CN3.2, Q3.3 (D), U26.6 (VIN2)
VBUS1: Q4.3 (D), U7.3, U26.3 (VIN1)

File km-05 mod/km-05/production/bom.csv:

Designator,Footprint,Quantity,Value,LCSC Part #
C1,0402,1,0.1u,
"C6, C7",0402,2,10u,
C8,0402,1,1u,
"CN1, CN10, CN11, CN12, CN14, CN2, CN4, CN5, CN6, CN7, CN8, CN9",SMD-1_BD2.0-H10.0,12,YTC1P-6030-01,C5221285
CN3,CONN-SMD_YZ199315035T-04025-01,1,Pogo Pin Receptor Right,C5296825
"Q3, Q4",SOT-23,2,AO3401A,
"R1, R2, R21, R22, R23, R24, R25, R26, R27, R28, R29, R3, R4",0402,13,10K,
"R10, R11, R12, R13, R14, R15, R16, R17, R18, R19, R20, R9",0402,12,0R,
"U1, U19, U20, U21, U22, U23, U24, U25",LED-SMD_4P-L3.5-W3.5-BR_SK6812MINI-HS,8,SK6812MINI-HS,C2922787
"U10, U11, U12, U13, U14, U15, U16, U17, U18, U3, U4, U5, U6, U9",DFN1006-2L-BI,14,H3V3U10B,C20615782
U2,VQFN-20-1EP_3x3mm_P0.4mm_EP1.7x1.7mm,1,ATtiny1616-M,
U26,SOT-583-8_L2.1-W1.2-P0.50-LS1.6-BL,1,LM66200DRLR,C3235556
U7,CONN-SMD_4P-L11.0-W5.5-P2.50_YZ165615055F-04025-01,1,Pogo Pin Left,C5296819
U8,SOT-23-5,1,AP2112K-3.3,

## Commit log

2025-12-22 added alpha src files & prototype files
2025-12-25 device discovery works
2025-12-31 beginning to create module chains
2026-01-15 added version 1.0 of kicad file for kh-24
    some eva inspired posters too, have fun
2026-01-15 created km-02 modwheels
2026-01-18 km-5 mostly finished
2026-01-31 work
2026-02-08 ptc stuff
2026-02-15 core mainboard
2026-02-18 many
2026-02-21 prod
2026-02-25 improved fuses
2026-02-27 hall faceplate
2026-03-01 faceplate designs
2026-03-21 production 1
2026-03-25 models
2026-03-30 xray
2026-04-25 bjnbnb
